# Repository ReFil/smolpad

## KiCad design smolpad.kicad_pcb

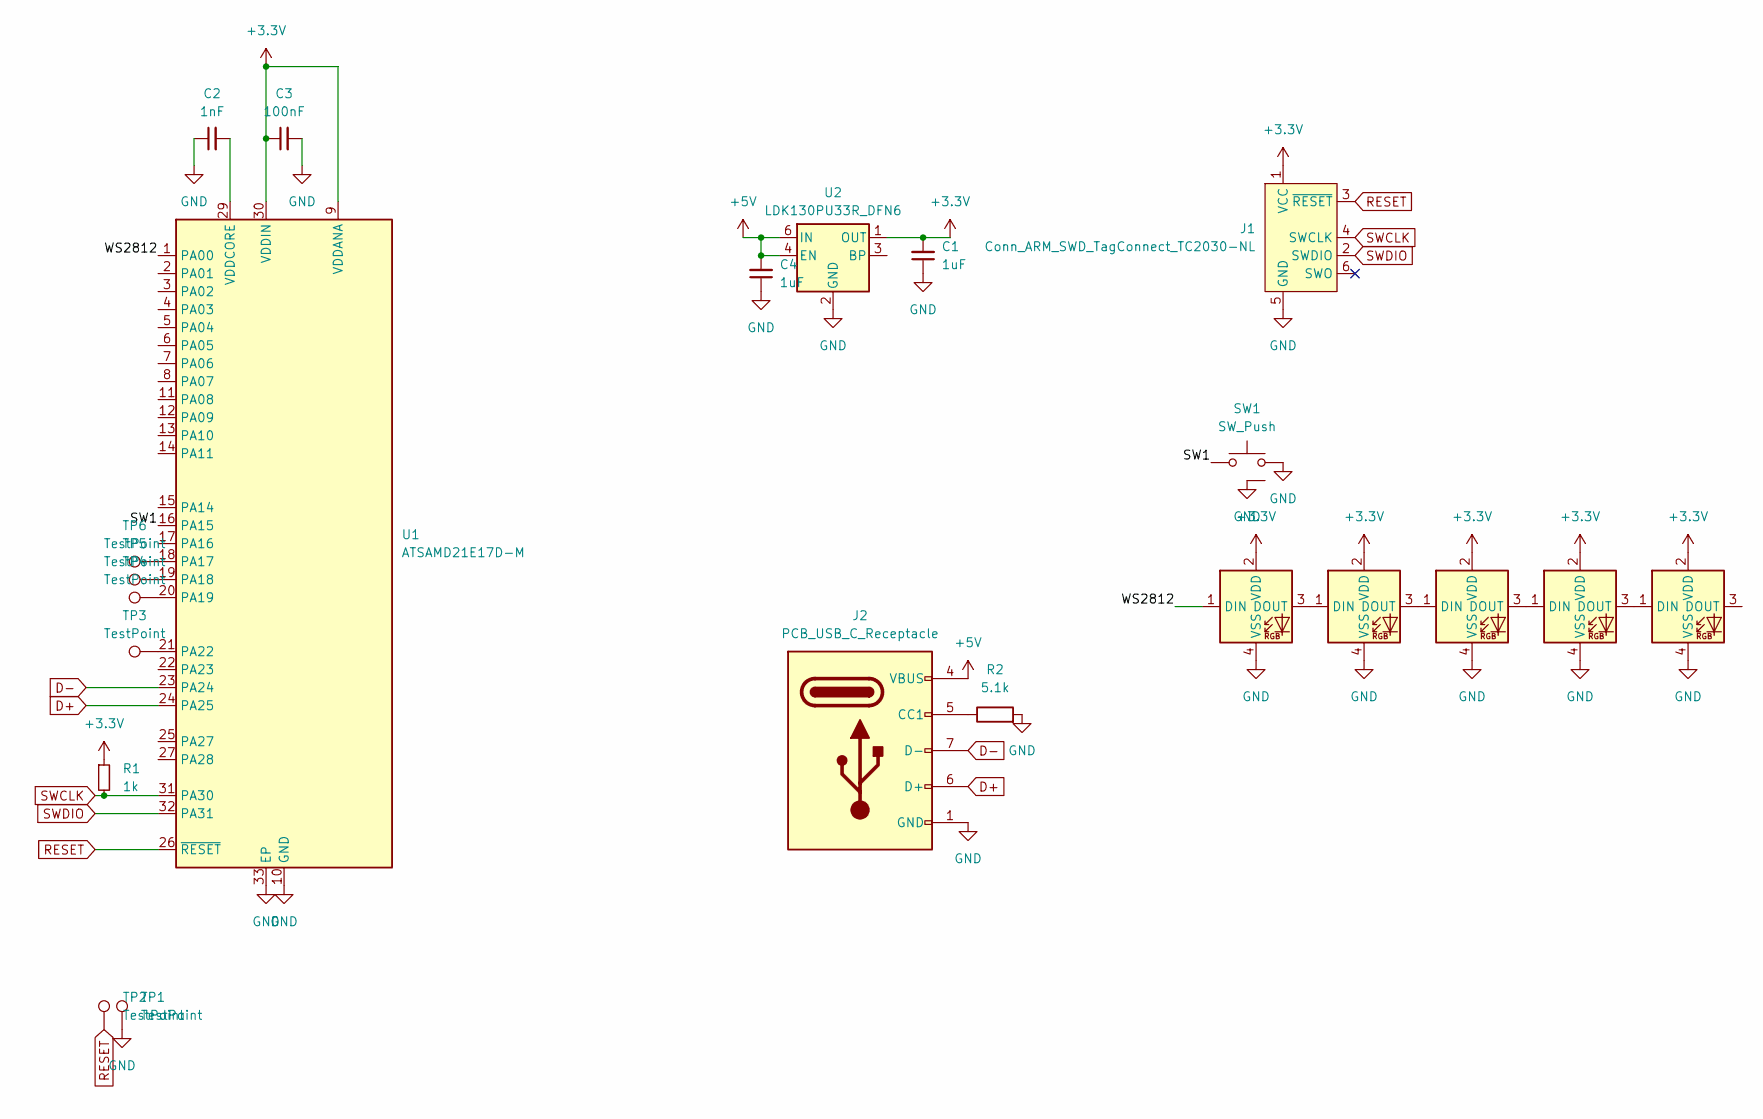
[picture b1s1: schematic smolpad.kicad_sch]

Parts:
C1, C4: 1uF; C_0402_1005Metric; LCSC Part Number C2169363
C2: 1nF; C_0402_1005Metric; LCSC Part Number C129637
C3: 100nF; C_0402_1005Metric; LCSC Part Number C2169363
J1: Conn_ARM_SWD_TagConnect_TC2030-NL; Tag-Connect_TC2030-IDC-NL_2x03_P1.27mm_Vertical
J2: PCB_USB_C_Receptacle; usb-c-one-sided
R1: 1k; R_0402_1005Metric
R2: 5.1k; R_0402_1005Metric
RGB1, RGB2, RGB3, RGB4, RGB5: SK6805-E-J
SW1: SW_Push; Cherry_ULP_SMD
TP1, TP2, TP3, TP4, TP5, TP6: TestPoint; TestPoint_Pad_1.0x1.0mm
U1: ATSAMD21E17D-M; QFN-32-1EP_5x5mm_P0.5mm_EP3.6x3.6mm
U2: LDK130PU33R_DFN6; DFN-6_1.3x1.2mm_P0.4mm

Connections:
+3.3V: C1.2, C3.1, J1.1 (VCC), R1.1, RGB1.2 (VDD), RGB2.2 (VDD), RGB3.2 (VDD), RGB4.2 (VDD), RGB5.2 (VDD), U1.9 (VDDANA), U1.30 (VDDIN), U2.1 (OUT)
+5V: C4.2, J2.4 (VBUS), J2.9 (VBUS), U2.4 (EN), U2.6 (IN)
/SW1: SW1.1, U1.16 (PA15)
/WS2812: RGB3.1 (DIN), U1.1 (PA00)
D+: J2.6 (D+), U1.24 (PA25)
D-: J2.7 (D-), U1.23 (PA24)
GND: C1.1, C2.1, C3.2, C4.1, J1.5 (GND), J2.1 (GND), J2.12 (GND), R2.2, RGB1.4 (VSS), RGB2.4 (VSS), RGB3.4 (VSS), RGB4.4 (VSS), RGB5.4 (VSS), SW1.2, SW1.3 (MP), TP1.1, U1.10 (GND), U1.28 (GND), U1.33 (EP), U2.2 (GND)
unnamed: J2.5 (CC1), R2.1
unnamed: RGB1.1 (DIN), RGB3.3 (DOUT)
unnamed: RGB1.3 (DOUT), RGB2.1 (DIN)
unnamed: RGB2.3 (DOUT), RGB4.1 (DIN)
unnamed: RGB4.3 (DOUT), RGB5.1 (DIN)
unnamed: TP6.1, U1.18 (PA17)
unnamed: TP5.1, U1.19 (PA18)
unnamed: TP4.1, U1.20 (PA19)
unnamed: TP3.1, U1.21 (PA22)
unnamed: C2.2, U1.29 (VDDCORE)
RESET: J1.3 (~RESET), TP2.1, U1.26 (~RESET)
SWCLK: J1.4 (SWCLK), R1.2, U1.31 (PA30)
SWDIO: J1.2 (SWDIO), U1.32 (PA31)

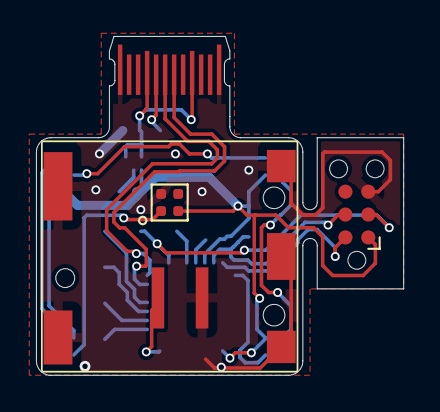
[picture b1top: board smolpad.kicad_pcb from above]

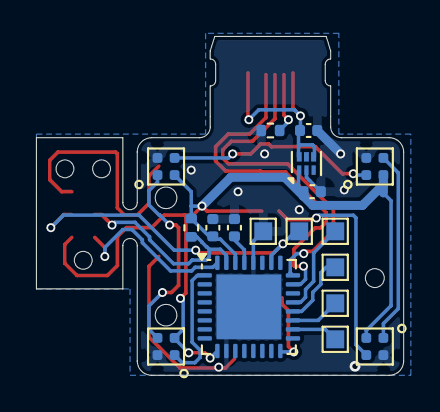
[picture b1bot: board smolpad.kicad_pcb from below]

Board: 2 copper layers, 20.4 x 18.8 mm, 22 parts (18 on the bottom side), 20 nets.

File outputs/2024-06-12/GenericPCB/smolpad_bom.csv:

"Value","Designator","Footprint","LCSC Part Number","Digikey Part Number","Comments"
"1nF","C2","C_0402_1005Metric","","",""
"100nF","C3","C_0402_1005Metric","","",""
"1uF","C1,C4","C_0402_1005Metric","","",""
"PCB_USB_C_Receptacle","J2","usb-c-one-sided","","",""
"1k","R1","R_0402_1005Metric","","",""
"5.1k","R2","R_0402_1005Metric","","",""
"SK6805-E-J","RGB1,RGB2,RGB3,RGB4,RGB5","SK6805-E-J","","",""
"SW_Push","SW1","Cherry_ULP_SMD","","",""
"ATSAMD21E17D-M","U1","QFN-32-1EP_5x5mm_P0.5mm_EP3.6x3.6mm","","",""
"LDK130PU33R_DFN6","U2","DFN-6_1.3x1.2mm_P0.4mm","","",""
